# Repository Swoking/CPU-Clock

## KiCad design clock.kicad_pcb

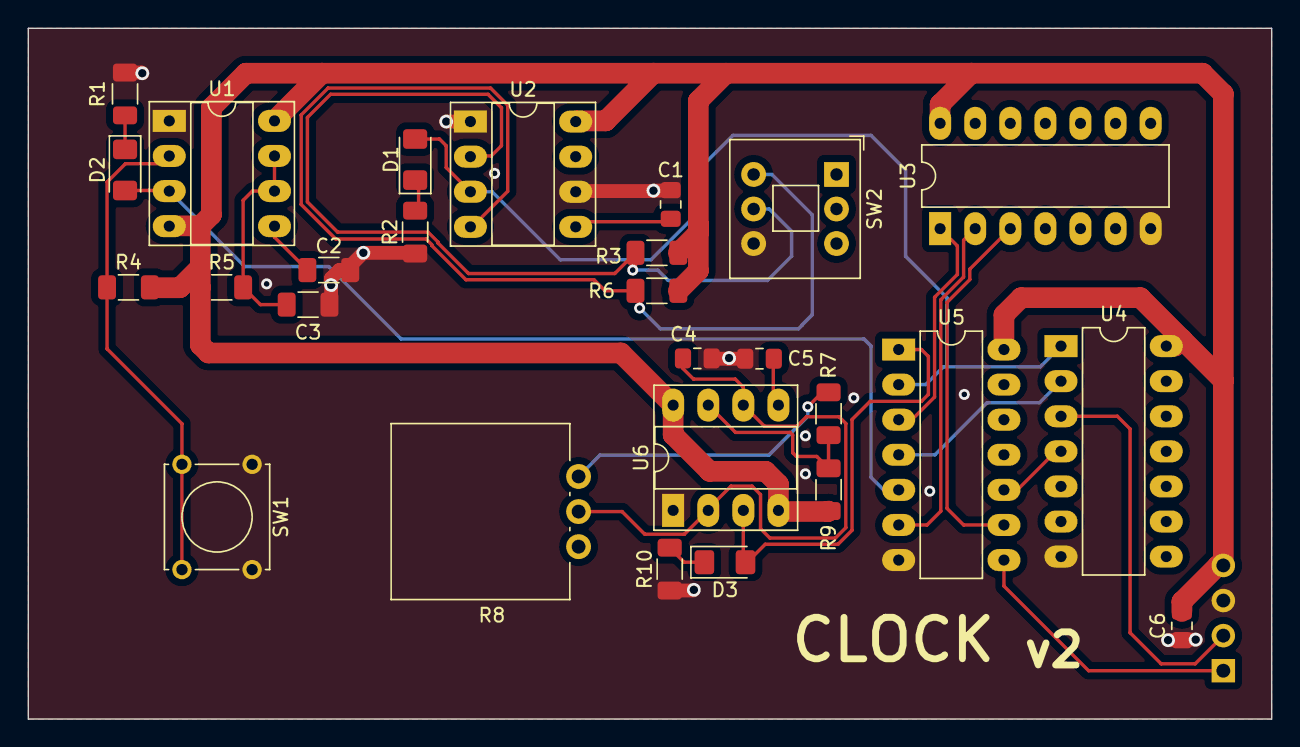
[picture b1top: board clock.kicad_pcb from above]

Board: 2 copper layers, 90.0 x 50.0 mm, 28 parts (1 on the bottom side), 25 nets.

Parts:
C1, C5: 0.01u; C_0805_2012Metric_Pad1.18x1.45mm_HandSolder
C2: 0.01u; R_1206_3216Metric_Pad1.30x1.75mm_HandSolder
C3: 0.1u; R_1206_3216Metric_Pad1.30x1.75mm_HandSolder
C4: 1u; C_0805_2012Metric_Pad1.18x1.45mm_HandSolder
C6: 0.1u; C_0805_2012Metric_Pad1.18x1.45mm_HandSolder
D1, D2, D3: LED; LED_1206_3216Metric_Pad1.42x1.75mm_HandSolder
J1: Conn_01x04; PinHeader_1x04_P2.54mm_Vertical
R1, R2, R10: 220; R_1206_3216Metric_Pad1.30x1.75mm_HandSolder
R3, R4, R6, R7, R9: 1k; R_1206_3216Metric_Pad1.30x1.75mm_HandSolder
R5: 1M; R_1206_3216Metric_Pad1.30x1.75mm_HandSolder
R8: 0-1M; Potentiometer_Vishay_248GJ-249GJ_Single_Vertical
SW1: SW_Push; SW_Tactile_Straight_KSL0Axx1LFTR
SW2: SW_Push_SPDT; SW_Push_2P2T_Toggle_CK_PVA2xxH1xxxxxxV2
U1, U2, U6: DIP-8_W7.62mm_Socket_LongPads
U3: 74LS32; DIP-14_W7.62mm_LongPads
U4: 74LS04; DIP-14_W7.62mm_LongPads
U5: 74LS08; DIP-14_W7.62mm_LongPads

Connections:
/Clock Logic/Out: D1.2 (A), U2.3 (OUT), U4.1, U5.2
/Clock Selector/Clock 1: D3.2 (A), U5.1, U6.3 (OUT)
/Clock Selector/Clock 2: D2.2 (A), U1.3 (OUT), U5.5
Clock: J1.1, U5.8
GND: C1.1, C2.1, C3.1, C4.1, C5.1, C6.2, J1.3, R1.1, R2.1, R10.1, SW1.1, SW2.6 (B), U1.1 (GND), U2.1 (GND), U2.6 (THRES), U3.7 (GND), U4.7 (GND), U5.7 (GND), U6.1 (GND)
HLT: J1.2, U4.3
unnamed: D1.1 (K), R2.2
unnamed: D2.1 (K), R1.2
unnamed: D3.1 (K), R10.2
unnamed: R7.2, R8.1
unnamed: R3.2, SW2.5 (A), U2.2 (TRIG)
unnamed: R6.2, SW2.4 (C), U2.4 (RESET)
unnamed: C2.2, U1.5 (CONT)
unnamed: C3.2, R5.2, U1.6 (THRES), U1.7 (DISCH)
unnamed: R4.1, SW1.2, U1.2 (TRIG)
unnamed: C1.2, U2.5 (CONT)
unnamed: U3.1, U5.3
unnamed: U3.2, U5.6
unnamed: U3.3, U5.9
unnamed: U4.2, U5.4
unnamed: U4.4, U5.10
unnamed: C5.2, U6.5 (CONT)
unnamed: R7.1, R9.2, U6.7 (DISCH)
unnamed: C4.2, R8.2, U6.2 (TRIG), U6.6 (THRES)
Vcc: C6.1, J1.4, R3.1, R4.2, R5.1, R6.1, R9.1, U1.4 (RESET), U1.8 (Vcc), U2.8 (Vcc), U3.14 (VCC), U4.14 (VCC), U5.14 (VCC), U6.4 (RESET), U6.8 (Vcc)

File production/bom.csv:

Designator,Footprint,Quantity,Value,LCSC Part #
"C1, C5",0805,2,0.01u,C3015138
C2,1206,1,0.01u,C3015138
C3,1206,1,0.1u,C5137467
C4,0805,1,1u,C2837735
C6,0805,1,0.1u,C5137467
"D1, D2, D3",1206,3,LED,C965799
J1,PinHeader_1x04_P2.54mm_Vertical,1,Conn_01x04,C5142856
"R1, R10, R2",1206,3,220,C2933642
"R3, R4, R6, R7, R9",1206,5,1k,C4410
R5,1206,1,1M,C352130
R8,Potentiometer_Vishay_248GJ-249GJ_Single_Vertical,1,0-1M,
SW1,SW_Tactile_Straight_KSL0Axx1LFTR,1,SW_Push,
SW2,SW_Push_2P2T_Toggle_CK_PVA2xxH1xxxxxxV2,1,SW_Push_SPDT,
"U1, U2, U6",DIP-8_W7.62mm_Socket_LongPads,3,~,C18164403
U3,DIP-14_W7.62mm_LongPads,1,74LS32,C521171
U4,DIP-14_W7.62mm_LongPads,1,74LS04,C513511
U5,DIP-14_W7.62mm_LongPads,1,74LS08,C521140

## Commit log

2024-05-31 Create test
2024-06-15 Fix non standard switch buton
